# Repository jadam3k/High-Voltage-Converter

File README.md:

This is a small, simple high-voltage generator project that demonstrates how to use the MC34063 DC-DC switching regulator. The device works from a +12 V source and employs a buck-boost topology to supply a high-voltage, low-current output (~250 V).

## PCB Status

The PCB has been fully designed and routed. All components have been connected, and the work is done. Everything went smoothly — this was a quick and simple project.

## Essential Components

<table><tbody><tr><td>Reference</td><td>Qty</td><td>Value</td></tr><tr><td>CN1</td><td>1</td><td>+12V/GND/GND/HV</td></tr><tr><td>IC1</td><td>1</td><td>MC34063 SMD</td></tr><tr><td>L1</td><td>1</td><td>180uH</td></tr><tr><td>Q1</td><td>1</td><td>STN3N40K3</td></tr><tr><td>D1</td><td>1</td><td>ES1G-13-F</td></tr><tr><td>C1</td><td>1</td><td>10uF 400V</td></tr><tr><td>C2</td><td>1</td><td>10uF 400V</td></tr><tr><td>Feedback Resistors (R4/R5)</td><td>2</td><td>470K / 47K</td></tr></tbody></table>

## How It Works

- **MC34063** is the component that manages the switching cycle.

 -L1 is the inductor where energy is stored when the MOSFET Q1 is ON, and it is later delivered to the output through diode D1 and capacitor C1 when Q1 is OFF.

- The capacitor C1 serves to even out the voltage of the output.

- The feedback resistors are used to keep the output voltage at the set value (~250 V).

## Images

### Schematic:

### PCB: 
|

### 3D VIEW:

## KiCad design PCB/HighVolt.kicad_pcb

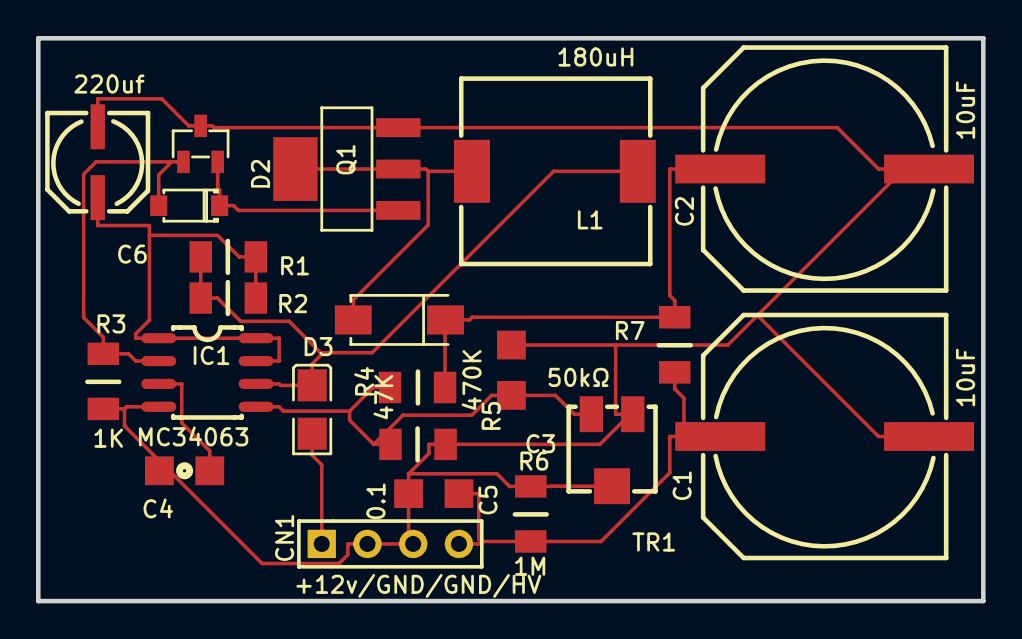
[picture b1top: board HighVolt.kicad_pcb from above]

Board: 2 copper layers, 52.5 x 31.3 mm, 22 parts (0 on the bottom side), 11 nets.

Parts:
C1, C2: 10uF; CAP-SMD_BD12.5-L13.0-W13.0-RD
C3: .01; C1206
C4: 470p; C1206
C5: 0.1; C1206
C6: 220uf; CAP-SMD_MED
CN1: +12v/GND/GND/HV; HDR-4X1/2.54
D1: ES1G-13-F; SMA_L4.4-W2.8-LS5.4-RD
D2: 1N4148FL; SOD-123_L2.8-W1.8-LS3.7-RD
D3: D1206 Diode GP; D1206-RD
IC1: MC34063; SOIC-8_L5.0-W4.0-P1.27-LS6.0-BL
L1: 180uH; IND-SMD_L10.5-W10.3_PSPHAQ104R
Q1: STN3N40K3; SOT-223_L6.5-W3.5-P2.30-LS7.0-BR
Q2: MMBT3906; SOT-23-3_L2.9-W1.3-P1.90-LS2.4-BR
R1, R2: 0.5; 1206
R3: 1K; 1206
R4: 470K; 1206
R5: 47K; 1206
R6: 1M; 1206
R7: 10K; 1206
TR1: 50kΩ; RES-ADJ-SMD_3P-L4.8-W4.6-P2.30-TR

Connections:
C1_1: C1.1, C5.1, CN1.4, R6.2, R7.2
COMP: C3.1, IC1.5, R4.1, R5.2, TR1.1
D1_1: C2.1, D1.1, R4.2, R7.1
D3_2: CN1.1, D3.2
GND: C1.2, C2.2, C3.2, C4.2, C5.2, C6.2, CN1.2, CN1.3, IC1.4, Q1.3, Q2.3, R3.2, R5.1, R6.1, TR1.2, TR1.3
IC1_1: C6.1, IC1.1, IC1.7, IC1.8, R1.1, R2.1
IC1_2: D2.2, IC1.2, Q2.1, R3.1
IC1_3: C4.1, IC1.3
IC1_6: D3.1, IC1.6, L1.1, R1.2, R2.2
Q1_1: D2.1, Q1.1, Q2.2
Q1_4: D1.2, L1.2, Q1.2, Q1.4

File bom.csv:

Reference,Qty,Value
C1,1,10uF 400V
C2,1,10uF 400V
C3,1,.01
C4,1,470p
C5,1,0.1 500V
C6,1,220uF
CN1,1,+12V/GND/GND/HV
D1,1,ES1G-13-F
D2,1,1N4148FL
D3,1,D1206 Diode GP
IC1,1,MC34063 SMD
L1,1,180uH
Q1,1,STN3N40K3
Q2,1,MMBT3906
R1,1,0.5
R2,1,0.5
R3,1,1K
R4,1,470K
R5,1,47K
R6,1,1M
R7,1,10K
RR1,1,50kΩ
